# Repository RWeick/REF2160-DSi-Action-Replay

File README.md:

# REF2160-DSi-Action-Replay
Full schematic, PCB Gerbers for the DSi Action Replay, and the rom

PCB Thickness: 0.8 mm

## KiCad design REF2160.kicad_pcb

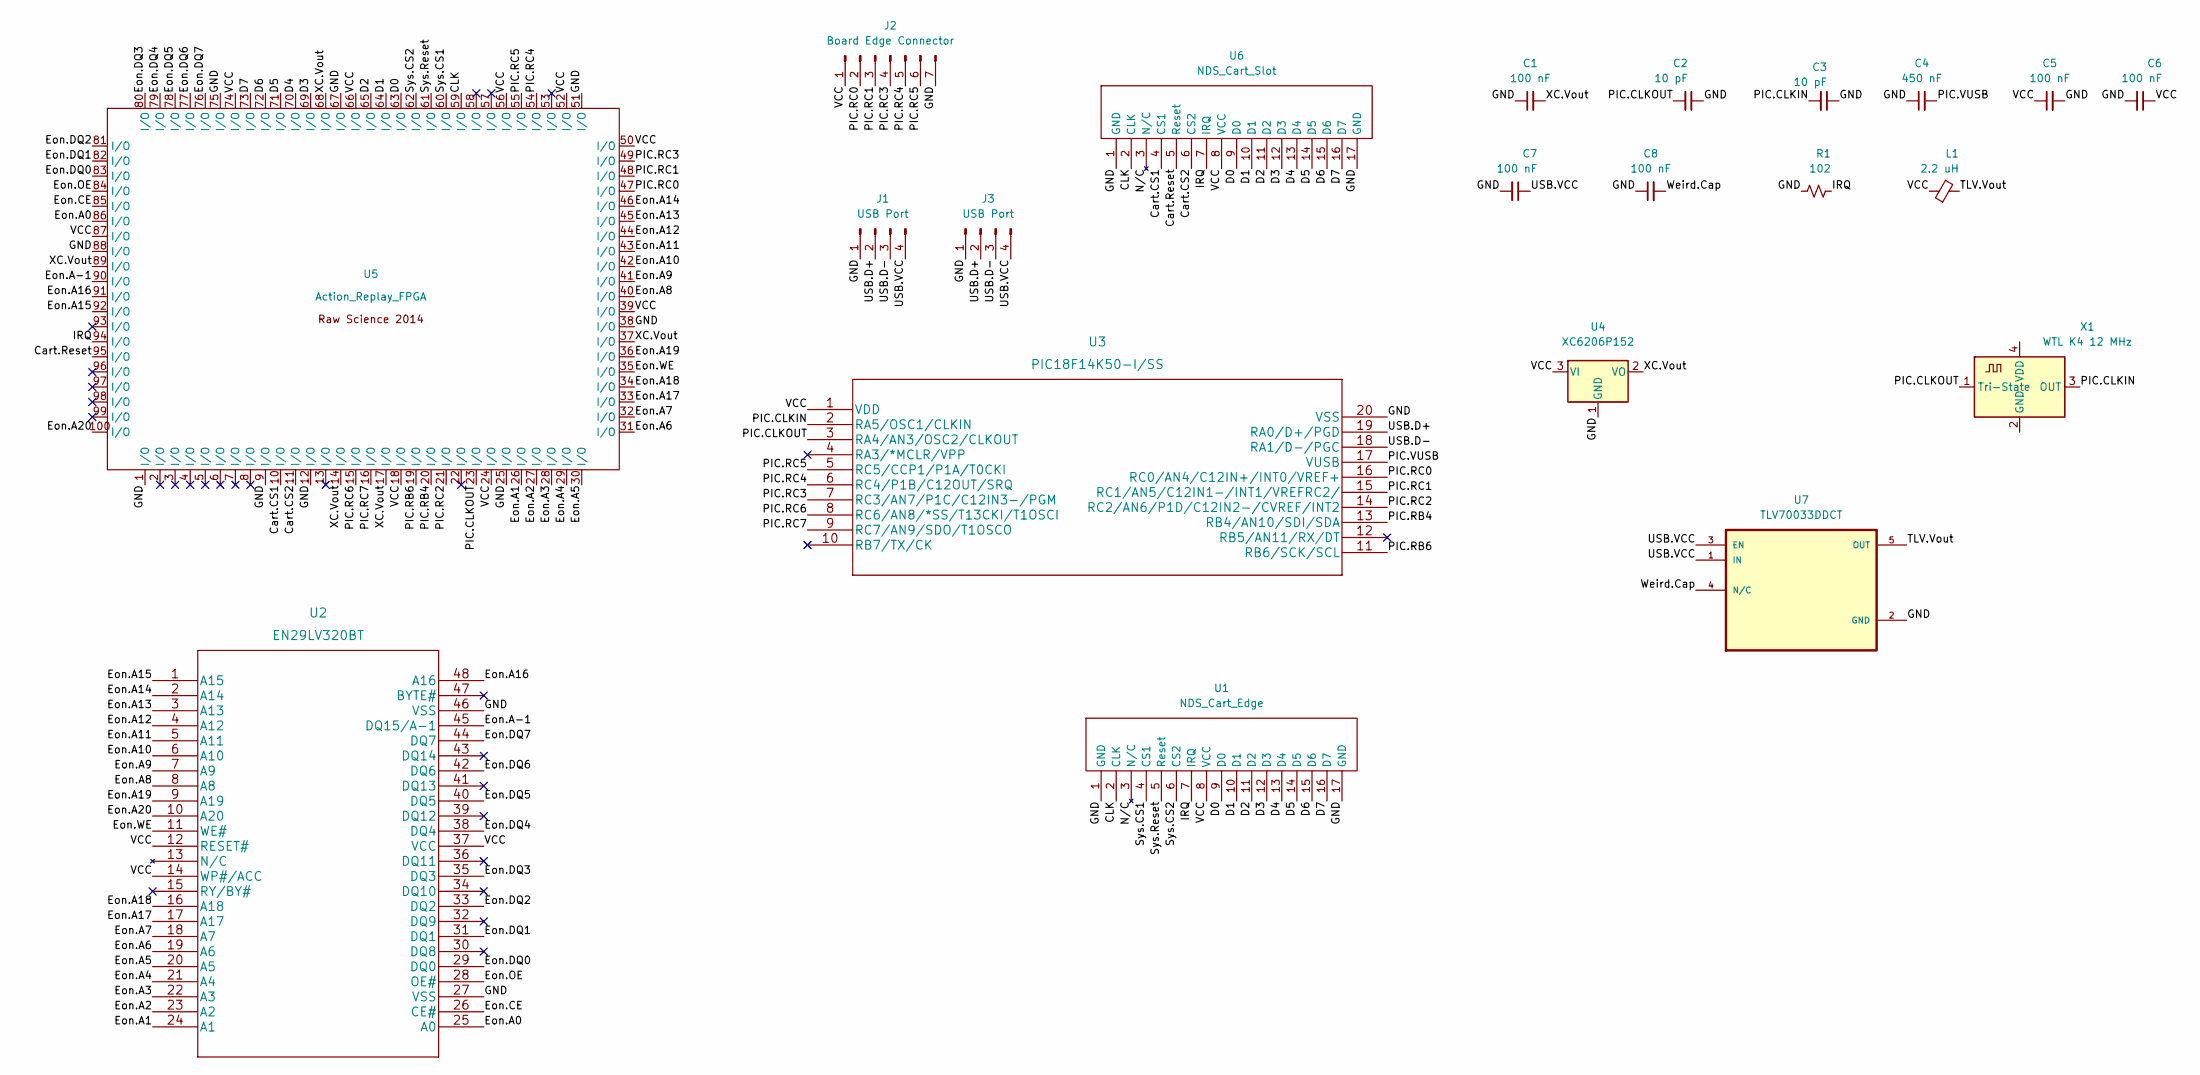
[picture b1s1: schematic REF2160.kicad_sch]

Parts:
C1: 100 nF; Big SMD
C2, C3: 10 pF; Little SMD
C4: 450 nF; Little SMD
C5, C6, C7, C8: 100 nF; Little SMD
J1, J3: USB Port; USB Adapter
J2: Board Edge Connector; Board Edge Rear Connector
L1: 2.2 uH; Ferrite Inductor
R1: 102; Little SMD
U1: NDS_Cart_Edge; Edge Connector
U2: EN29LV320BT; SOP50P2000X120-48N
U3: PIC18F14K50-I/SS; PIC18F14K50-I&slash_SS
U4: XC6206P152; 65E9 SOT-23
U5: Action_Replay_FPGA; Raw Science FPGA
U6: NDS_Cart_Slot; DS Slot
U7: TLV70033DDCT; ODN SOT-23-5
X1: WTL K4 12 MHz; Clock

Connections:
/CLK: U1.2 (CLK), U5.59 (I/O), U6.2 (CLK)
/Cart.CS1: U5.10 (I/O), U6.4 (CS1)
/Cart.CS2: U5.11 (I/O), U6.6 (CS2)
/Cart.Reset: U5.95 (I/O), U6.5 (Reset)
/D0: U1.9 (D0), U5.63 (I/O), U6.9 (D0)
/D1: U1.10 (D1), U5.64 (I/O), U6.10 (D1)
/D2: U1.11 (D2), U5.65 (I/O), U6.11 (D2)
/D3: U1.12 (D3), U5.69 (I/O), U6.12 (D3)
/D4: U1.13 (D4), U5.70 (I/O), U6.13 (D4)
/D5: U1.14 (D5), U5.71 (I/O), U6.14 (D5)
/D6: U1.15 (D6), U5.72 (I/O), U6.15 (D6)
/D7: U1.16 (D7), U5.73 (I/O), U6.16 (D7)
/Eon.A0: U2.25 (A0), U5.86 (I/O)
/Eon.A1: U2.24 (A1), U5.26 (I/O)
/Eon.A2: U2.23 (A2), U5.27 (I/O)
/Eon.A3: U2.22 (A3), U5.28 (I/O)
/Eon.A4: U2.21 (A4), U5.29 (I/O)
/Eon.A5: U2.20 (A5), U5.30 (I/O)
/Eon.A6: U2.19 (A6), U5.31 (I/O)
/Eon.A7: U2.18 (A7), U5.32 (I/O)
/Eon.A8: U2.8 (A8), U5.40 (I/O)
/Eon.A9: U2.7 (A9), U5.41 (I/O)
/Eon.A10: U2.6 (A10), U5.42 (I/O)
/Eon.A11: U2.5 (A11), U5.43 (I/O)
/Eon.A12: U2.4 (A12), U5.44 (I/O)
/Eon.A13: U2.3 (A13), U5.45 (I/O)
/Eon.A14: U2.2 (A14), U5.46 (I/O)
/Eon.A15: U2.1 (A15), U5.92 (I/O)
/Eon.A16: U2.48 (A16), U5.91 (I/O)
/Eon.A17: U2.17 (A17), U5.33 (I/O)
/Eon.A18: U2.16 (A18), U5.34 (I/O)
/Eon.A19: U2.9 (A19), U5.36 (I/O)
/Eon.A20: U2.10 (A20), U5.100 (I/O)
/Eon.A-1: U2.45 (DQ15/A-1), U5.90 (I/O)
/Eon.CE: U2.26 (CE#), U5.85 (I/O)
/Eon.DQ0: U2.29 (DQ0), U5.83 (I/O)
/Eon.DQ1: U2.31 (DQ1), U5.82 (I/O)
/Eon.DQ2: U2.33 (DQ2), U5.81 (I/O)
/Eon.DQ3: U2.35 (DQ3), U5.80 (I/O)
/Eon.DQ4: U2.38 (DQ4), U5.79 (I/O)
/Eon.DQ5: U2.40 (DQ5), U5.78 (I/O)
/Eon.DQ6: U2.42 (DQ6), U5.77 (I/O)
/Eon.DQ7: U2.44 (DQ7), U5.76 (I/O)
/Eon.OE: U2.28 (OE#), U5.84 (I/O)
/Eon.WE: U2.11 (WE#), U5.35 (I/O)
/GND: C1.1, C2.2, C3.2, C4.1, C5.2, C6.2, C7.2, C8.1, J1.1, J2.7, J3.1, R1.2, U1.1 (GND), U1.17 (GND), U2.27 (VSS), U2.46 (VSS), U3.20 (VSS), U4.1 (GND), U5.1 (I/O), U5.9 (I/O), U5.12 (I/O), U5.25 (I/O), U5.38 (I/O), U5.51 (I/O), U5.67 (I/O), U5.75 (I/O), U5.88 (I/O), U6.1 (GND), U6.17 (GND), U7.2 (GND)
/IRQ: R1.1, U1.7 (IRQ), U5.94 (I/O), U6.7 (IRQ)
/PIC.CLKIN: C3.1, U3.2 (RA5/OSC1/CLKIN), X1.3 (OUT)
/PIC.CLKOUT: C2.1, U3.3 (RA4/AN3/OSC2/CLKOUT), U5.23 (I/O), X1.1 (Tri-State)
/PIC.RB4: U3.13 (RB4/AN10/SDI/SDA), U5.20 (I/O)
/PIC.RB6: U3.11 (RB6/SCK/SCL), U5.19 (I/O)
/PIC.RC0: J2.2, U3.16 (RC0/AN4/C12IN+/INT0/VREF+), U5.47 (I/O)
/PIC.RC1: J2.3, U3.15 (RC1/AN5/C12IN1-/INT1/VREFRC2/), U5.48 (I/O)
/PIC.RC2: U3.14 (RC2/AN6/P1D/C12IN2-/CVREF/INT2), U5.21 (I/O)
/PIC.RC3: J2.4, U3.7 (RC3/AN7/P1C/C12IN3-/PGM), U5.49 (I/O)
/PIC.RC4: J2.5, U3.6 (RC4/P1B/C12OUT/SRQ), U5.54 (I/O)
/PIC.RC5: J2.6, U3.5 (RC5/CCP1/P1A/T0CKI), U5.55 (I/O)
/PIC.RC6: U3.8 (RC6/AN8/*SS/T13CKI/T1OSCI), U5.15 (I/O)
/PIC.RC7: U3.9 (RC7/AN9/SDO/T1OSCO), U5.16 (I/O)
/PIC.VUSB: C4.2, U3.17 (VUSB)
/Sys.CS1: U1.4 (CS1), U5.60 (I/O)
/Sys.CS2: U1.6 (CS2), U5.62 (I/O)
/Sys.Reset: U1.5 (Reset), U5.61 (I/O)
/TLV.Vout: L1.2, U7.5 (OUT)
/USB.D+: J1.2, J3.2, U3.19 (RA0/D+/PGD)
/USB.D-: J1.3, J3.3, U3.18 (RA1/D-/PGC)
/USB.VCC: C7.1, J1.4, J3.4, U7.1 (IN), U7.3 (EN)
/VCC: C5.1, C6.1, J2.1, L1.1, U1.8 (VCC), U2.12 (RESET#), U2.14 (WP#/ACC), U2.37 (VCC), U3.1 (VDD), U4.3 (VI), U5.18 (I/O), U5.24 (I/O), U5.39 (I/O), U5.50 (I/O), U5.52 (I/O), U5.56 (I/O), U5.66 (I/O), U5.74 (I/O), U5.87 (I/O), U6.8 (VCC)
/Weird.Cap: C8.2, U7.4 (N/C)
/XC.Vout: C1.2, U4.2 (VO), U5.14 (I/O), U5.17 (I/O), U5.37 (I/O), U5.68 (I/O), U5.89 (I/O)

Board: 4 copper layers, 23 parts (4 on the bottom side), 70 nets, no tracks yet.

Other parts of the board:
H1, H2: MountingHole_2.1mm

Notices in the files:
parts and their libraries:
Copyright 2021 Accelerated Designs. All rights reserved.
